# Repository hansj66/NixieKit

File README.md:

# Nixie Clock Kit 1.3

This repository contains firmware examples and the necessary STEP files for completing the TimeExpander Nixie Clock Kit. 

You will need to patch the 595 driver for the wiringPi and invert the logic before compiling the firmware.

The PDF in the "doc" folder contains assembly instructions / bill of materials

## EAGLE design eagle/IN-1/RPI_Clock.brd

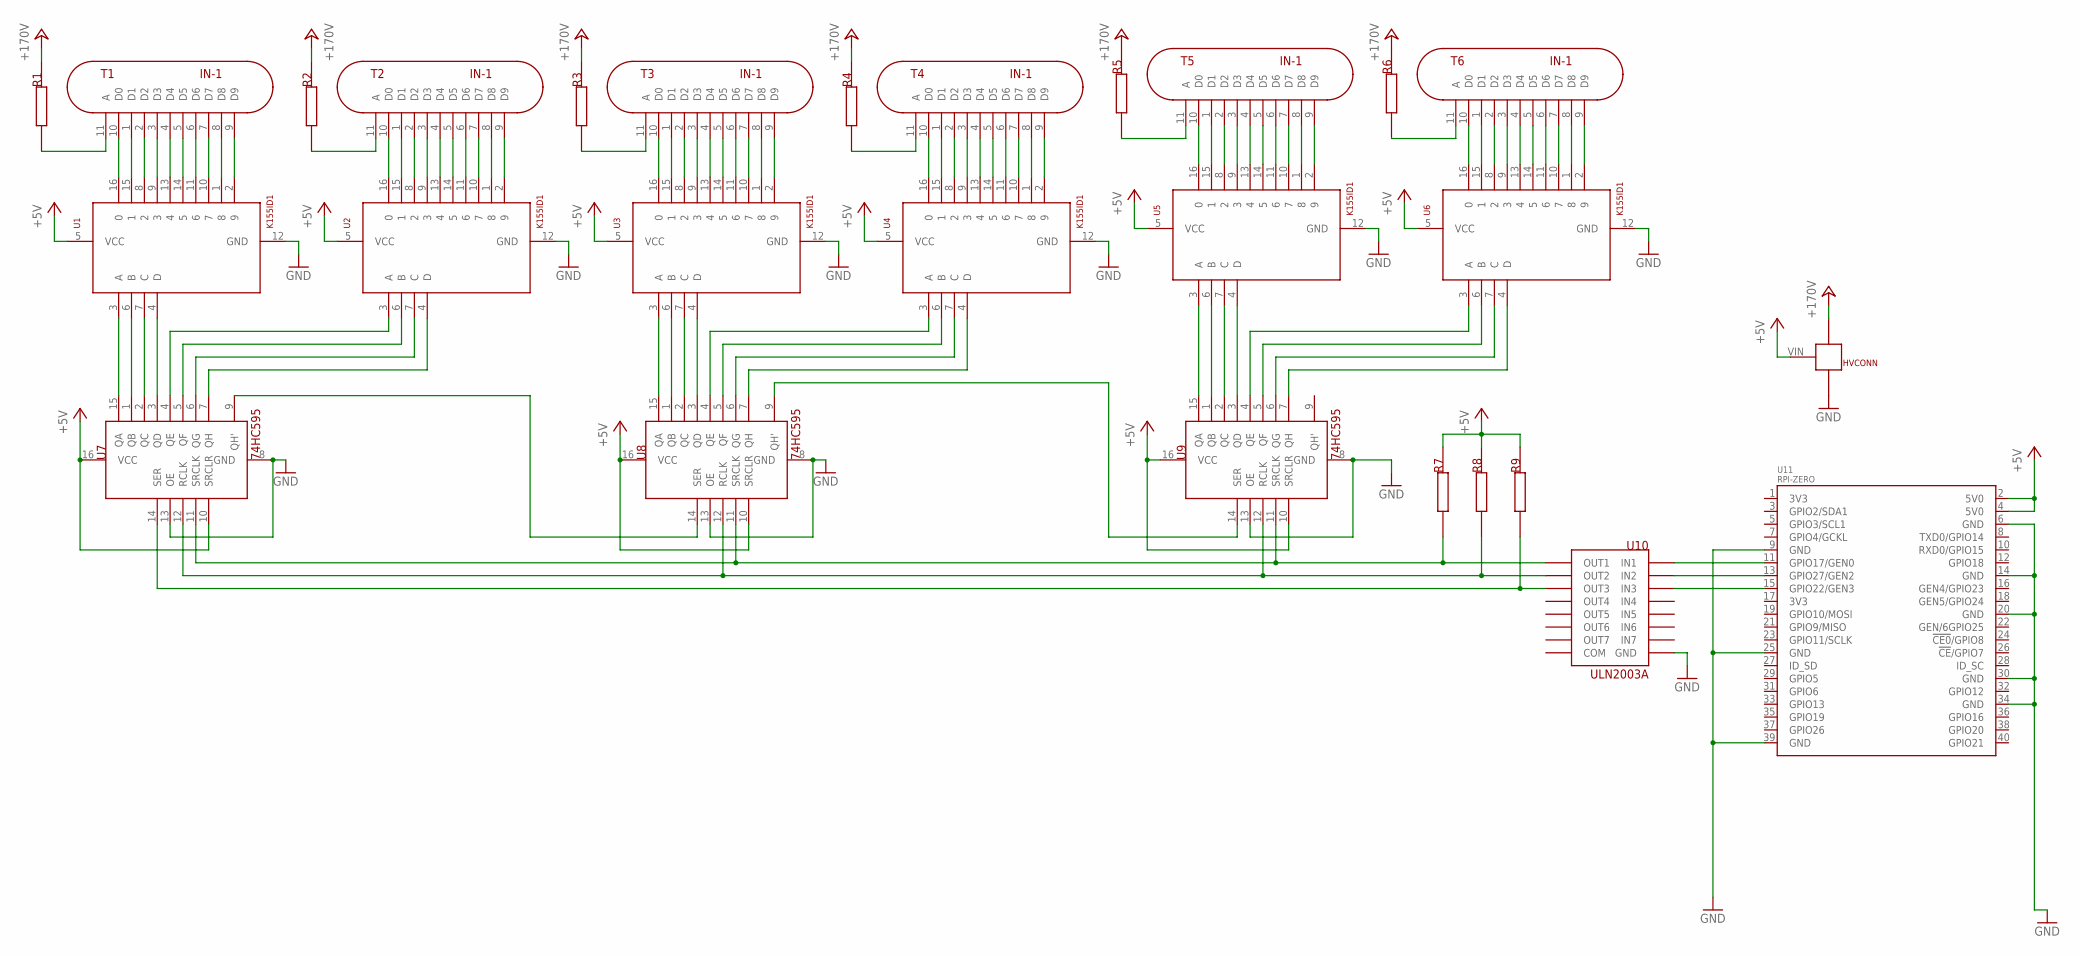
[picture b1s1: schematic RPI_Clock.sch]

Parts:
HVCONN: HV_CONNECTOR
R1, R2, R3, R4, R5, R6: 5,6K; ANODE_RESISTOR
R7, R8, R9: 10k; ANODE_RESISTOR
T1, T2, T3, T4, T5, T6: IN-1
U1, U2, U3, U4, U5, U6: K155ID1; DIP16-2.54-19.2X7.62MM
U7, U8, U9: 74HC595; DIL16
U10: ULN2003A; DIL16
U11: RPI-ZERO; RASP_PI_ZERO_BOARD_FULL

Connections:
+5V: HVCONN.VIN, R7.P$2, R8.P$2, R9.P$2, U1.5 (VCC), U2.5 (VCC), U3.5 (VCC), U4.5 (VCC), U5.5 (VCC), U6.5 (VCC), U7.10 (SRCLR), U7.16 (VCC), U8.10 (SRCLR), U8.16 (VCC), U9.10 (SRCLR), U9.16 (VCC), U11.2 (5V0), U11.4 (5V0)
+24V: HVCONN.+170V, R1.P$2, R2.P$2, R3.P$2, R4.P$2, R5.P$2, R6.P$2
GND: HVCONN.GND, U1.12 (GND), U2.12 (GND), U3.12 (GND), U4.12 (GND), U5.12 (GND), U6.12 (GND), U7.8 (GND), U7.13 (OE), U8.8 (GND), U8.13 (OE), U9.8 (GND), U9.13 (OE), U10.8 (GND), U11.6 (GND), U11.9 (GND), U11.14 (GND), U11.20 (GND), U11.25 (GND), U11.30 (GND), U11.34 (GND), U11.39 (GND)
unnamed: T1.9 (D9), U1.2 (9)
unnamed: T1.8 (D8), U1.1 (8)
unnamed: T1.7 (D7), U1.10 (7)
unnamed: T1.6 (D6), U1.11 (6)
unnamed: T1.5 (D5), U1.14 (5)
unnamed: T1.4 (D4), U1.13 (4)
unnamed: T1.3 (D3), U1.9 (3)
unnamed: T1.2 (D2), U1.8 (2)
unnamed: T1.1 (D1), U1.15 (1)
unnamed: T1.10 (D0), U1.16 (0)
unnamed: R1.P$1, T1.11 (A)
unnamed: T2.9 (D9), U2.2 (9)
unnamed: T2.8 (D8), U2.1 (8)
unnamed: T2.7 (D7), U2.10 (7)
unnamed: T2.6 (D6), U2.11 (6)
unnamed: T2.5 (D5), U2.14 (5)
unnamed: T2.4 (D4), U2.13 (4)
unnamed: T2.3 (D3), U2.9 (3)
unnamed: T2.2 (D2), U2.8 (2)
unnamed: T2.1 (D1), U2.15 (1)
unnamed: T2.10 (D0), U2.16 (0)
unnamed: R2.P$1, T2.11 (A)
unnamed: T3.9 (D9), U3.2 (9)
unnamed: T3.8 (D8), U3.1 (8)
unnamed: T3.7 (D7), U3.10 (7)
unnamed: T3.6 (D6), U3.11 (6)
unnamed: T3.5 (D5), U3.14 (5)
unnamed: T3.4 (D4), U3.13 (4)
unnamed: T3.3 (D3), U3.9 (3)
unnamed: T3.2 (D2), U3.8 (2)
unnamed: T3.1 (D1), U3.15 (1)
unnamed: T3.10 (D0), U3.16 (0)
unnamed: R3.P$1, T3.11 (A)
unnamed: T4.9 (D9), U4.2 (9)
unnamed: T4.8 (D8), U4.1 (8)
unnamed: T4.7 (D7), U4.10 (7)
unnamed: T4.6 (D6), U4.11 (6)
unnamed: T4.5 (D5), U4.14 (5)
unnamed: T4.4 (D4), U4.13 (4)
unnamed: T4.3 (D3), U4.9 (3)
unnamed: T4.2 (D2), U4.8 (2)
unnamed: T4.1 (D1), U4.15 (1)
unnamed: T4.10 (D0), U4.16 (0)
unnamed: R4.P$1, T4.11 (A)
unnamed: U10.1 (IN1), U11.11 (GPIO17/GEN0)
unnamed: U10.2 (IN2), U11.13 (GPIO27/GEN2)
unnamed: R7.P$1, U7.11 (SRCLK), U8.11 (SRCLK), U9.11 (SRCLK), U10.16 (OUT1)
unnamed: R8.P$1, U7.12 (RCLK), U8.12 (RCLK), U9.12 (RCLK), U10.15 (OUT2)
unnamed: R9.P$1, U7.14 (SER), U10.14 (OUT3)
unnamed: U10.3 (IN3), U11.15 (GPIO22/GEN3)
unnamed: T5.9 (D9), U5.2 (9)
unnamed: T5.8 (D8), U5.1 (8)
unnamed: T5.7 (D7), U5.10 (7)
unnamed: T5.6 (D6), U5.11 (6)
unnamed: T5.5 (D5), U5.14 (5)
unnamed: T5.4 (D4), U5.13 (4)
unnamed: T5.3 (D3), U5.9 (3)
unnamed: T5.2 (D2), U5.8 (2)
unnamed: T5.1 (D1), U5.15 (1)
unnamed: T5.10 (D0), U5.16 (0)
unnamed: R5.P$1, T5.11 (A)
unnamed: U1.3 (A), U7.15 (QA)
unnamed: U1.6 (B), U7.1 (QB)
unnamed: U1.7 (C), U7.2 (QC)
unnamed: U1.4 (D), U7.3 (QD)
unnamed: U2.3 (A), U7.4 (QE)
unnamed: U2.6 (B), U7.5 (QF)
unnamed: U2.7 (C), U7.6 (QG)
unnamed: U2.4 (D), U7.7 (QH)
unnamed: U3.3 (A), U8.15 (QA)
unnamed: U3.6 (B), U8.1 (QB)
unnamed: U3.7 (C), U8.2 (QC)
unnamed: U3.4 (D), U8.3 (QD)
unnamed: U4.3 (A), U8.4 (QE)
unnamed: U4.6 (B), U8.5 (QF)
unnamed: U4.7 (C), U8.6 (QG)
unnamed: U4.4 (D), U8.7 (QH)
unnamed: T6.9 (D9), U6.2 (9)
unnamed: T6.8 (D8), U6.1 (8)
unnamed: T6.7 (D7), U6.10 (7)
unnamed: T6.6 (D6), U6.11 (6)
unnamed: T6.5 (D5), U6.14 (5)
unnamed: T6.4 (D4), U6.13 (4)
unnamed: T6.3 (D3), U6.9 (3)
unnamed: T6.2 (D2), U6.8 (2)
unnamed: U7.9 (QH'), U8.14 (SER)
unnamed: T6.1 (D1), U6.15 (1)
unnamed: T6.10 (D0), U6.16 (0)
unnamed: R6.P$1, T6.11 (A)
unnamed: U5.3 (A), U9.15 (QA)
unnamed: U5.6 (B), U9.1 (QB)
unnamed: U5.7 (C), U9.2 (QC)
unnamed: U5.4 (D), U9.3 (QD)
unnamed: U6.3 (A), U9.4 (QE)
unnamed: U6.6 (B), U9.5 (QF)
unnamed: U6.7 (C), U9.6 (QG)
unnamed: U6.4 (D), U9.7 (QH)
unnamed: U8.9 (QH'), U9.14 (SER)

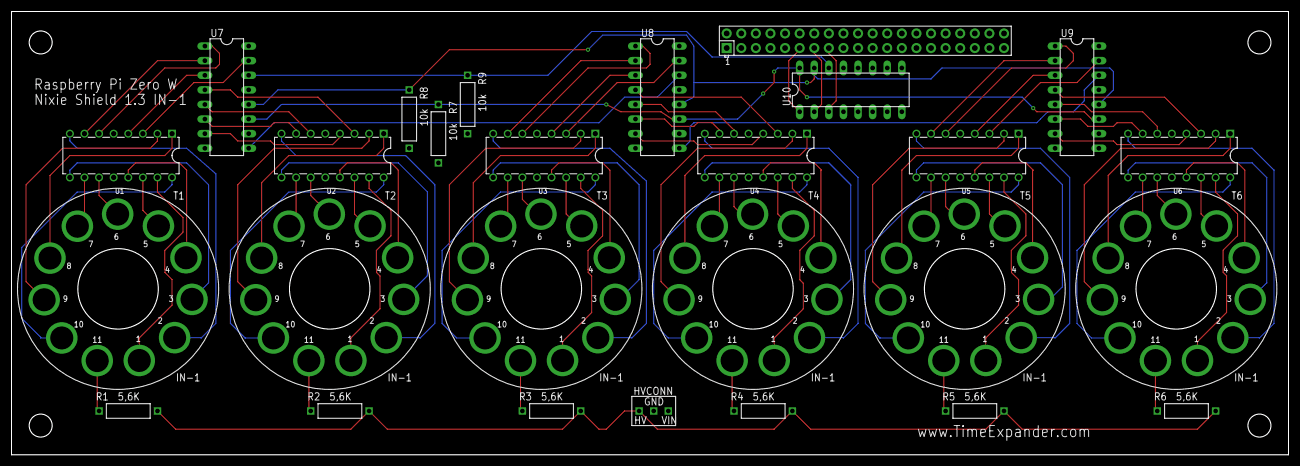
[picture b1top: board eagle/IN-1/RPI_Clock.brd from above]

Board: 4 copper layers, 222.2 x 77.1 mm, 27 parts (0 on the bottom side), 101 nets.

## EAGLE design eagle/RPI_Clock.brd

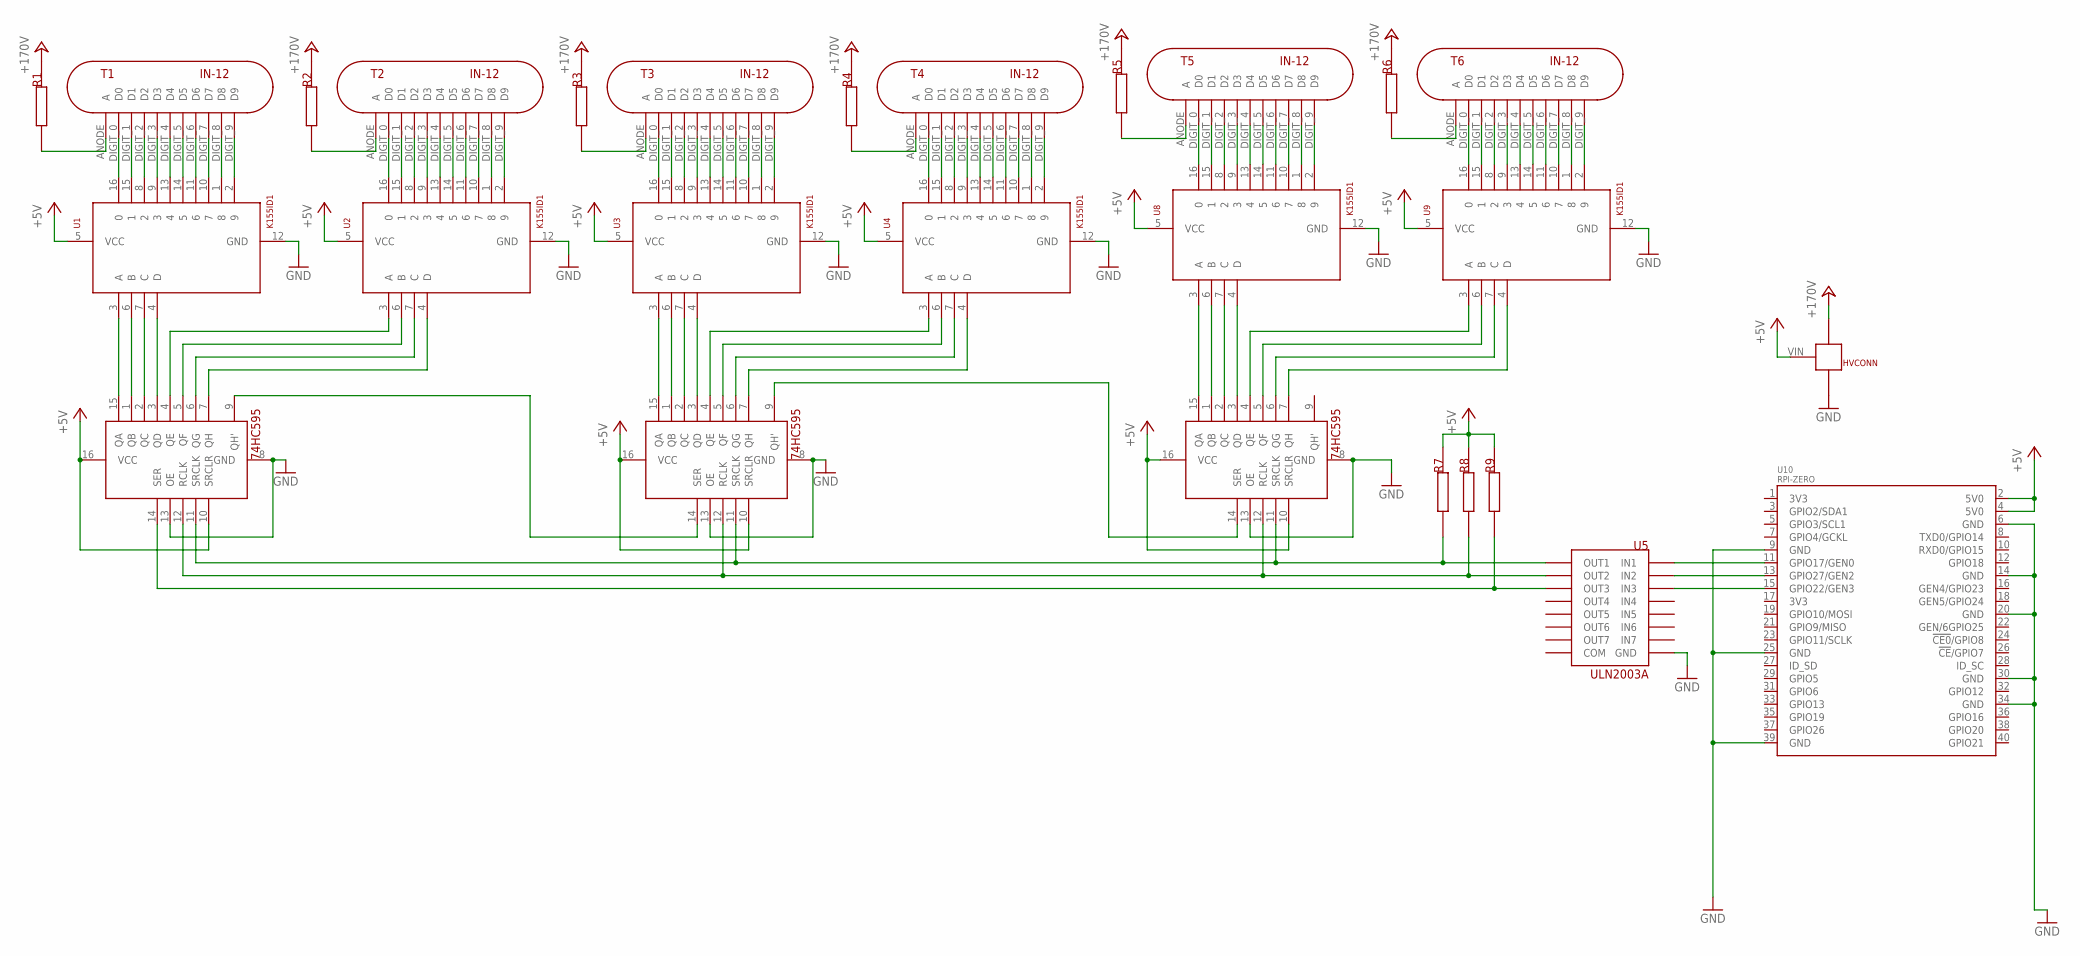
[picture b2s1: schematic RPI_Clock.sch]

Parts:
HVCONN: HV_CONNECTOR
R1, R2, R3, R4, R5, R6: 5,6K; ANODE_RESISTOR
R7, R8, R9: 10k; ANODE_RESISTOR
T1, T2, T3, T4, T5, T6: IN-12
U1, U2, U3, U4, U8, U9: K155ID1; DIP16-2.54-19.2X7.62MM
U5: ULN2003A; DIL16
U6, U7, U11: 74HC595; DIL16
U10: RPI-ZERO; RASP_PI_ZERO_BOARD_FULL

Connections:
+5V: HVCONN.VIN, R7.P$2, R8.P$2, R9.P$2, U1.5 (VCC), U2.5 (VCC), U3.5 (VCC), U4.5 (VCC), U6.10 (SRCLR), U6.16 (VCC), U7.10 (SRCLR), U7.16 (VCC), U8.5 (VCC), U9.5 (VCC), U10.2 (5V0), U10.4 (5V0), U11.10 (SRCLR), U11.16 (VCC)
+24V: HVCONN.+170V, R1.P$2, R2.P$2, R3.P$2, R4.P$2, R5.P$2, R6.P$2
GND: HVCONN.GND, U1.12 (GND), U2.12 (GND), U3.12 (GND), U4.12 (GND), U5.8 (GND), U6.8 (GND), U6.13 (OE), U7.8 (GND), U7.13 (OE), U8.12 (GND), U9.12 (GND), U10.6 (GND), U10.9 (GND), U10.14 (GND), U10.20 (GND), U10.25 (GND), U10.30 (GND), U10.34 (GND), U10.39 (GND), U11.8 (GND), U11.13 (OE)
unnamed: T1.DIGIT_9 (D9), U1.2 (9)
unnamed: T1.DIGIT_8 (D8), U1.1 (8)
unnamed: T1.DIGIT_7 (D7), U1.10 (7)
unnamed: T1.DIGIT_6 (D6), U1.11 (6)
unnamed: T1.DIGIT_5 (D5), U1.14 (5)
unnamed: T1.DIGIT_4 (D4), U1.13 (4)
unnamed: T1.DIGIT_3 (D3), U1.9 (3)
unnamed: T1.DIGIT_2 (D2), U1.8 (2)
unnamed: T1.DIGIT_1 (D1), U1.15 (1)
unnamed: T1.DIGIT_0 (D0), U1.16 (0)
unnamed: R1.P$1, T1.ANODE (A)
unnamed: T2.DIGIT_9 (D9), U2.2 (9)
unnamed: T2.DIGIT_8 (D8), U2.1 (8)
unnamed: T2.DIGIT_7 (D7), U2.10 (7)
unnamed: T2.DIGIT_6 (D6), U2.11 (6)
unnamed: T2.DIGIT_5 (D5), U2.14 (5)
unnamed: T2.DIGIT_4 (D4), U2.13 (4)
unnamed: T2.DIGIT_3 (D3), U2.9 (3)
unnamed: T2.DIGIT_2 (D2), U2.8 (2)
unnamed: T2.DIGIT_1 (D1), U2.15 (1)
unnamed: T2.DIGIT_0 (D0), U2.16 (0)
unnamed: R2.P$1, T2.ANODE (A)
unnamed: T3.DIGIT_9 (D9), U3.2 (9)
unnamed: T3.DIGIT_8 (D8), U3.1 (8)
unnamed: T3.DIGIT_7 (D7), U3.10 (7)
unnamed: T3.DIGIT_6 (D6), U3.11 (6)
unnamed: T3.DIGIT_5 (D5), U3.14 (5)
unnamed: T3.DIGIT_4 (D4), U3.13 (4)
unnamed: T3.DIGIT_3 (D3), U3.9 (3)
unnamed: T3.DIGIT_2 (D2), U3.8 (2)
unnamed: T3.DIGIT_1 (D1), U3.15 (1)
unnamed: T3.DIGIT_0 (D0), U3.16 (0)
unnamed: R3.P$1, T3.ANODE (A)
unnamed: T4.DIGIT_9 (D9), U4.2 (9)
unnamed: T4.DIGIT_8 (D8), U4.1 (8)
unnamed: T4.DIGIT_7 (D7), U4.10 (7)
unnamed: T4.DIGIT_6 (D6), U4.11 (6)
unnamed: T4.DIGIT_5 (D5), U4.14 (5)
unnamed: T4.DIGIT_4 (D4), U4.13 (4)
unnamed: T4.DIGIT_3 (D3), U4.9 (3)
unnamed: T4.DIGIT_2 (D2), U4.8 (2)
unnamed: T4.DIGIT_1 (D1), U4.15 (1)
unnamed: T4.DIGIT_0 (D0), U4.16 (0)
unnamed: R4.P$1, T4.ANODE (A)
unnamed: U5.1 (IN1), U10.11 (GPIO17/GEN0)
unnamed: U5.2 (IN2), U10.13 (GPIO27/GEN2)
unnamed: R7.P$1, U5.16 (OUT1), U6.11 (SRCLK), U7.11 (SRCLK), U11.11 (SRCLK)
unnamed: R8.P$1, U5.15 (OUT2), U6.12 (RCLK), U7.12 (RCLK), U11.12 (RCLK)
unnamed: R9.P$1, U5.14 (OUT3), U6.14 (SER)
unnamed: U5.3 (IN3), U10.15 (GPIO22/GEN3)
unnamed: T5.DIGIT_9 (D9), U8.2 (9)
unnamed: T5.DIGIT_8 (D8), U8.1 (8)
unnamed: T5.DIGIT_7 (D7), U8.10 (7)
unnamed: T5.DIGIT_6 (D6), U8.11 (6)
unnamed: T5.DIGIT_5 (D5), U8.14 (5)
unnamed: T5.DIGIT_4 (D4), U8.13 (4)
unnamed: T5.DIGIT_3 (D3), U8.9 (3)
unnamed: T5.DIGIT_2 (D2), U8.8 (2)
unnamed: T5.DIGIT_1 (D1), U8.15 (1)
unnamed: T5.DIGIT_0 (D0), U8.16 (0)
unnamed: R5.P$1, T5.ANODE (A)
unnamed: U1.3 (A), U6.15 (QA)
unnamed: U1.6 (B), U6.1 (QB)
unnamed: U1.7 (C), U6.2 (QC)
unnamed: U1.4 (D), U6.3 (QD)
unnamed: U2.3 (A), U6.4 (QE)
unnamed: U2.6 (B), U6.5 (QF)
unnamed: U2.7 (C), U6.6 (QG)
unnamed: U2.4 (D), U6.7 (QH)
unnamed: U3.3 (A), U7.15 (QA)
unnamed: U3.6 (B), U7.1 (QB)
unnamed: U3.7 (C), U7.2 (QC)
unnamed: U3.4 (D), U7.3 (QD)
unnamed: U4.3 (A), U7.4 (QE)
unnamed: U4.6 (B), U7.5 (QF)
unnamed: U4.7 (C), U7.6 (QG)
unnamed: U4.4 (D), U7.7 (QH)
unnamed: T6.DIGIT_9 (D9), U9.2 (9)
unnamed: T6.DIGIT_8 (D8), U9.1 (8)
unnamed: T6.DIGIT_7 (D7), U9.10 (7)
unnamed: T6.DIGIT_6 (D6), U9.11 (6)
unnamed: T6.DIGIT_5 (D5), U9.14 (5)
unnamed: T6.DIGIT_4 (D4), U9.13 (4)
unnamed: T6.DIGIT_3 (D3), U9.9 (3)
unnamed: T6.DIGIT_2 (D2), U9.8 (2)
unnamed: U6.9 (QH'), U7.14 (SER)
unnamed: T6.DIGIT_1 (D1), U9.15 (1)
unnamed: T6.DIGIT_0 (D0), U9.16 (0)
unnamed: R6.P$1, T6.ANODE (A)
unnamed: U8.3 (A), U11.15 (QA)
unnamed: U8.6 (B), U11.1 (QB)
unnamed: U8.7 (C), U11.2 (QC)
unnamed: U8.4 (D), U11.3 (QD)
unnamed: U9.3 (A), U11.4 (QE)
unnamed: U9.6 (B), U11.5 (QF)
unnamed: U9.7 (C), U11.6 (QG)
unnamed: U9.4 (D), U11.7 (QH)
unnamed: U7.9 (QH'), U11.14 (SER)

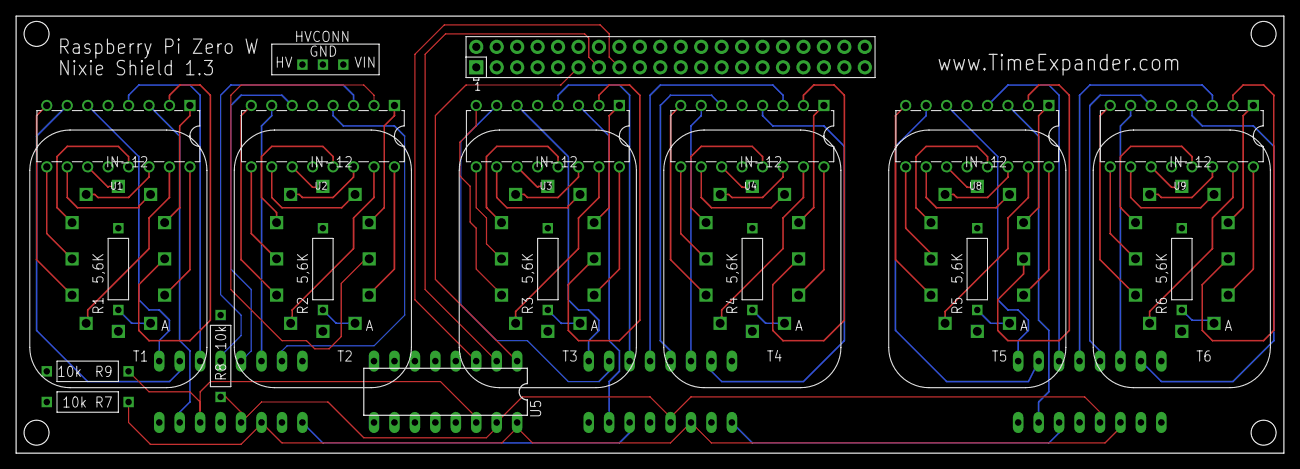
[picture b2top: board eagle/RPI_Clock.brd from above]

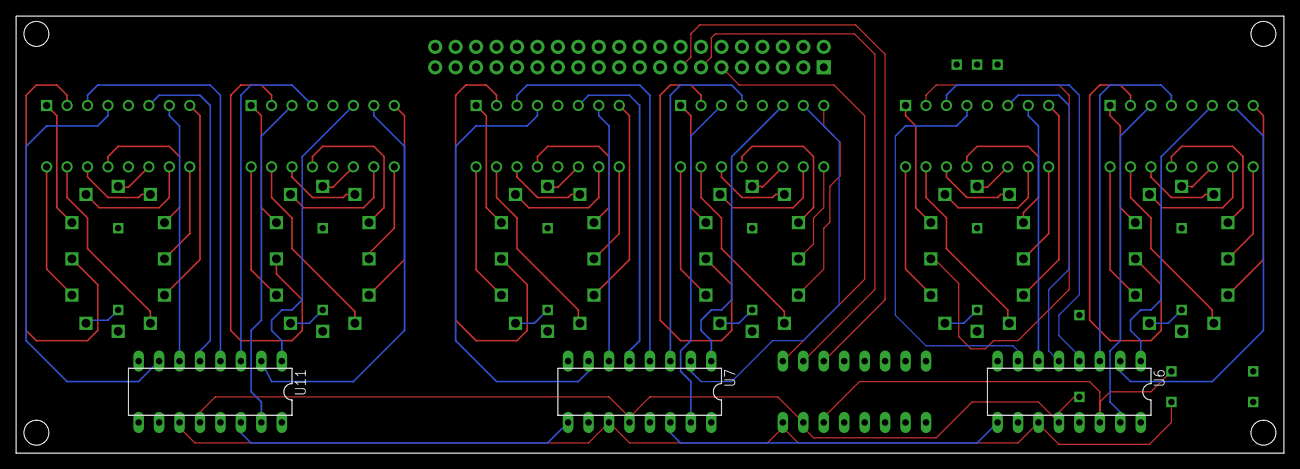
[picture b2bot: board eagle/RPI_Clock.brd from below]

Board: 4 copper layers, 157.5 x 54.3 mm, 27 parts (3 on the bottom side), 101 nets.

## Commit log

2019-12-27 Added firmware example and STEP files
2021-09-13 Added Eagle CAD files
    * Added bill of materials and assembly instructions
2021-09-13 Added images
2021-09-13 Fixed jpg extension
2021-09-22 Updated Eagle design files with 1.3 version
2021-09-22 Added modified 595 driver for wiringPi
    * Necessary beacuse of the ULN2003 (inverting logic)
2021-09-23 Added DXF files for enclosures
    * Also added alternative enclosure
2021-12-28 Added experimental IN-1 variant of the nixie clock
2021-12-28 Added library with nixie symbols and footprints
    * IN-1
    * IN-2
    * IN-12
